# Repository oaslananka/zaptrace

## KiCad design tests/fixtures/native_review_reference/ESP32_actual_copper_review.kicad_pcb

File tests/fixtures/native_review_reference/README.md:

# Pinned native Review Studio source fixture

Read-only local ESP32/Issue #91 review inputs retained for repeatable tests. The original ignored `build/source-reference-readonly/` workspace remains untouched; tests use this distinct fixture copy. Do not treat native DRC/ERC output, stored copper, supplier shapes or generated libraries as fabrication approval.

The YAML, PCB and schematic retain their verified local SHA-256 digests. Run `sha256sum -c SHA256SUMS` from this directory before source-sensitive validation. KiCad `.kicad_prl` and lock files are intentionally excluded.

The original local build-script checksum file, `checksums.sha256`, is retained and
covered by the outer `SHA256SUMS` manifest.

Text-only project metadata and one upstream footprint file use canonical LF/EOF formatting in the committed test fixture; the original ignored local source files remain unchanged. The manifest hashes describe the committed fixture bytes.

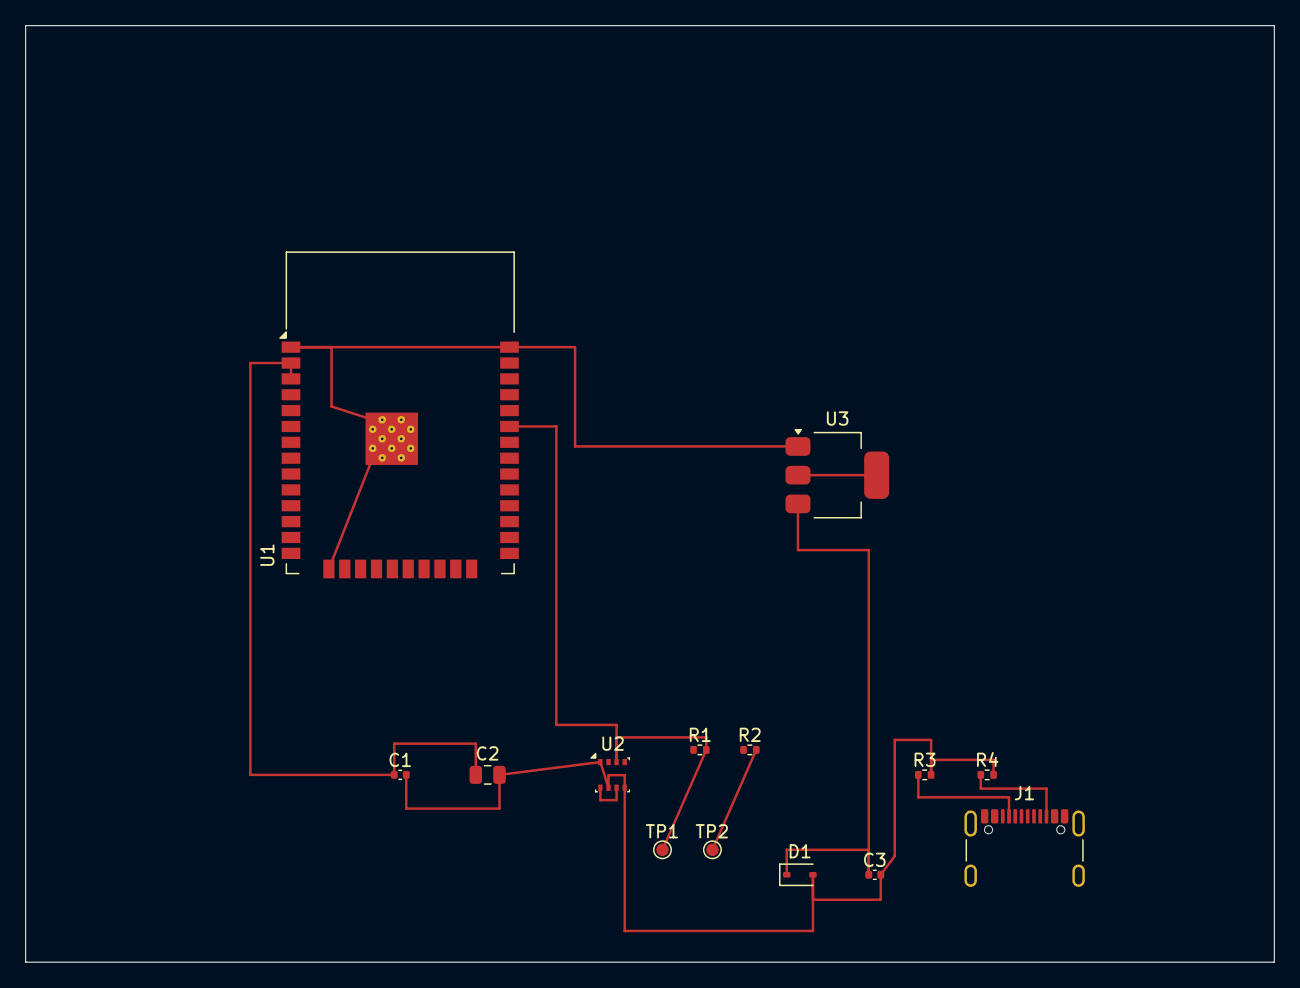
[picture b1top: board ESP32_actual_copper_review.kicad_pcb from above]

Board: 2 copper layers, 100.0 x 75.0 mm, 14 parts (0 on the bottom side), 7 nets.

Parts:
C1, C3: 100nF; C_0402_1005Metric
C2: 10uF; C_0805_2012Metric
D1: PESD5V0S1BA; D_SOD-323
J1: USB_C_Receptacle_GCT_USB4105-xx-A_16P_TopMnt_Hori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; USB_C_Receptacle_GCT_USB4105-xx-A_16P_TopMnt_Horizontal
R1, R2: 4.7k; R_0402_1005Metric
R3, R4: 5.1k; R_0402_1005Metric
TP1, TP2: TestPoint_Pad_D1.0mm
U1: ESP32-WROOM-32
U2: Bosch_LGA-8_2.5x2.5mm_P0.65mm_ClockwisePinNumberi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; Bosch_LGA-8_2.5x2.5mm_P0.65mm_ClockwisePinNumbering
U3: SOT-223-3_TabPin2

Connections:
GND: C1.2, C2.2, C3.2, D1.2, J1.A1, J1.A12, J1.B1, J1.B12, R3.2, R4.2, U1.1, U1.15, U1.38, U1.39, U2.1, U2.5, U2.7, U3.1
I2C_SCL: R2.2, TP2.1, U1.36, U2.4
I2C_SDA: R1.2, TP1.1, U1.33, U2.3
USB_CC1: J1.A5, R3.1
USB_CC2: J1.B5, R4.1
VCC_3V3: C1.1, C2.1, R1.1, R2.1, U1.2, U1.3, U2.2, U2.6, U2.8, U3.2
VCC_5V: C3.1, D1.1, J1.A4, J1.A9, J1.B4, J1.B9, U3.3
